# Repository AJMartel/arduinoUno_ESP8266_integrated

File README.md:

# Arduino UNO with built in ESP8266 Wifi Module
Arduino UNO with built in ESP8266 Wifi Module and 3.3v logic converter (pin outs added)

Created for 16Hertz LLC. 
Creative Commons Attribution/Non-Commercial/Share-Alike

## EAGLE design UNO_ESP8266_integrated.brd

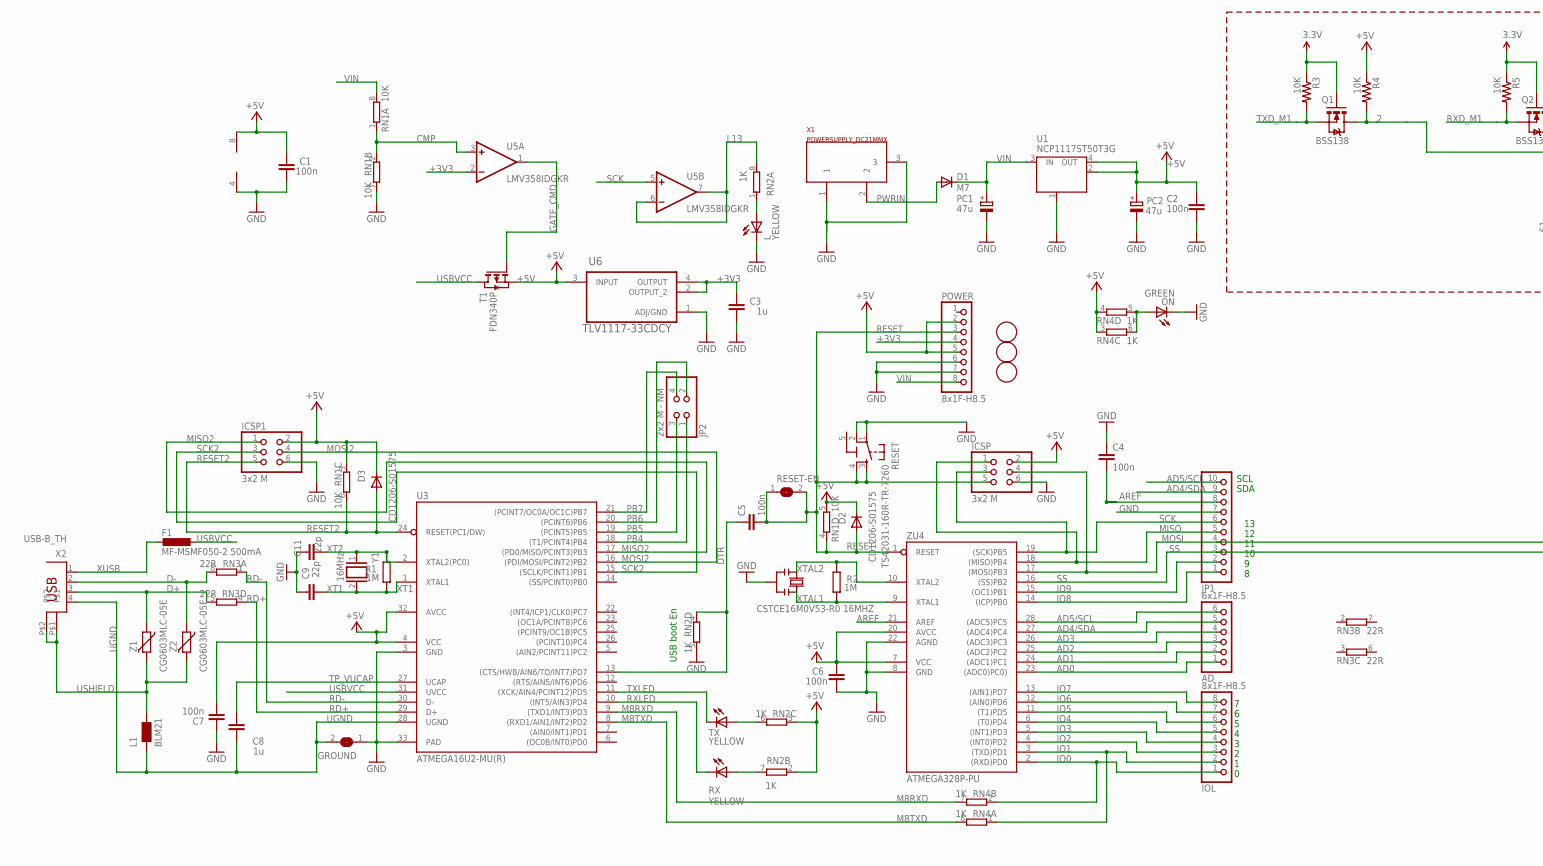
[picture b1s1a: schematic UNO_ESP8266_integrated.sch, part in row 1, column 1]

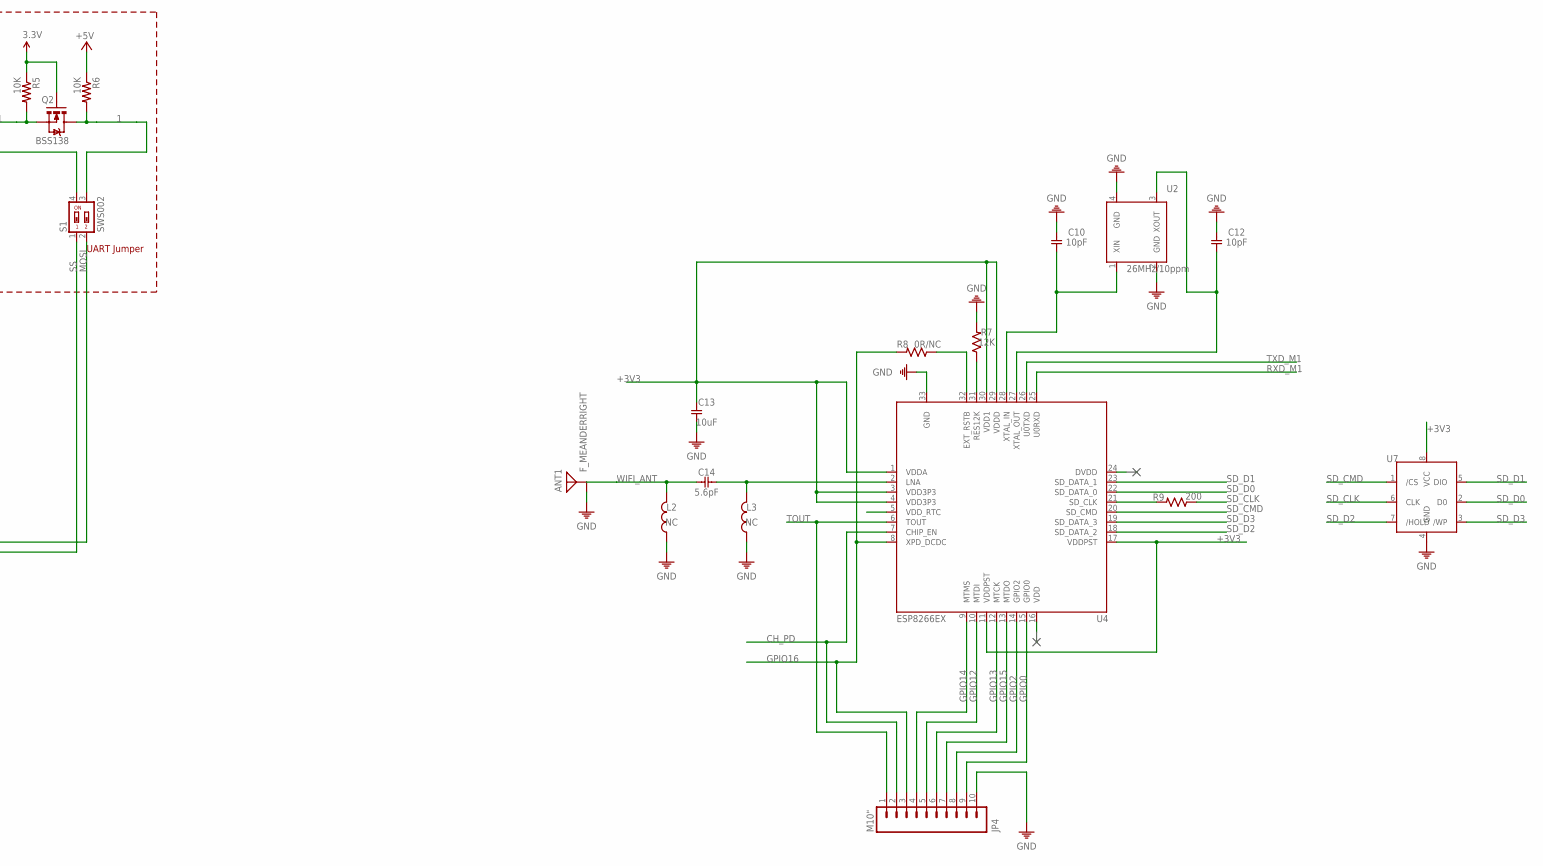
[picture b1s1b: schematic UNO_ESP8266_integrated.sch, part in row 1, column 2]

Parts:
AD: 6x1F-H8.5; 1X06
ANT1: F_MEANDERRIGHT; F_MEANDER_RIGHT
C1, C2, C4, C5, C6, C7: 100n; C0603-ROUND
C3, C8: 1u; C0603-ROUND
C9, C11: 22p; C0603-ROUND
C10, C12: 10pF; C0402
C13: 10uF; C0402
C14: 5.6pF; C0402
D1: M7; SMB
D2, D3: CD1206-S01575; MINIMELF
F1: MF-MSMF050-2 500mA; L1812
FD1, FD2, FD3: FIDUCIALMOUNT; FIDUCIA-MOUNT
GROUND: SJ
ICSP, ICSP1: 3x2 M; 2X03
IOL: 8x1F-H8.5; 1X08
JP1: PINHD-1X10_ARD; 1X10
JP2: 2x2 M - NM; 2X02
JP4: M10"; 1X10
L: YELLOW; CHIP-LED0805
L1: BLM21; 0805
L2, L3: NC; FB0603
ON: GREEN; CHIP-LED0805
PC1, PC2: 47u; PANASONIC_D
POWER: 8x1F-H8.5; 1X08
Q1, Q2: BSS138; SOT23-3
R1, R2: 1M; R0603-ROUND
R3, R4, R5, R6: 10K; 0603-RES
R7: 12K; R0402
R8: 0R/NC; R0402
R9: 200; R0402
RESET: TS42031-160R-TR-7260; TS42
RESET-EN: SJ
RN1: 10K; CAY16
RN2, RN4: 1K; CAY16
RN3: 22R; CAY16
RX: YELLOW; CHIP-LED0805
S1: SWS002; SMS-002
T1: FDN340P; SOT-23
TX: YELLOW; CHIP-LED0805
U1: NCP1117ST50T3G; SOT223
U2: 26MHz/10ppm; CRYSTAL_32X25
U3: ATMEGA16U2-MU(R); MLF32
U4: ESP8266EX; QFN32
U5: LMV358IDGKR; MSOP08
U6: TLV1117-33CDCY; SOT230P700X180-4N
U7: SPI_FLASH; SOIC-8
X1: POWERSUPPLY_DC21MMX; POWERSUPPLY_DC-21MM
X2: USB-B_TH; PN61729
Y1: 16MHz; QS
Y2: CSTCE16M0V53-R0 16MHZ; RESONATOR
Z1, Z2: CG0603MLC-05E; CT/CN0603
ZU4: ATMEGA328P-PU; DIL28-3

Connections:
1: Q2.3 (D), R6.2, S1.3
2: Q1.3 (D), R4.2, S1.4
5-GND: RESET.5 (5-GND)
+3V3: C3.2, C13.2, POWER.4, Q1.1 (G), Q2.1 (G), R3.1, R5.1, U4.1 (VDDA), U4.3 (VDD3P3), U4.4 (VDD3P3), U4.11 (VDDPST), U4.17 (VDDPST), U4.29 (VDDD), U4.30 (VDD1), U5.2 (-IN), U6.2 (OUTPUT_2), U6.4 (OUTPUT), U7.8 (VCC)
+5V: C1.2, C2.2, C6.2, C7.1, D2.C, D3.C, ICSP.2, ICSP1.2, PC2.+, POWER.2, POWER.5, R4.1, R6.1, RN1.3 (1), RN1.5 (2), RN2.2 (1), RN2.3 (1), RN4.3 (1), RN4.4 (1), T1.2 (S), U1.2 (OUT), U1.4 (OUT), U3.4 (VCC), U3.32 (AVCC), U5.8 (V+), U6.3 (INPUT), ZU4.7 (VCC), ZU4.20 (AVCC)
AD0: AD.1, ZU4.23 ((ADC0)PC0))
AD1: AD.2, ZU4.24 ((ADC1)PC1)
AD2: AD.3, ZU4.25 ((ADC2)PC2)
AD3: AD.4, ZU4.26 ((ADC3)PC3)
AD4/SDA: AD.5, JP1.9, ZU4.27 ((ADC4)PC4)
AD5/SCL: AD.6, JP1.10, ZU4.28 ((ADC5)PC5)
AREF: C4.2, JP1.8, ZU4.21 (AREF)
CH_PD: JP4.2, U4.7 (CHIP_EN)
CMP: RN1.1, RN1.2 (1), U5.3 (+IN)
D+: RN3.5 (2), X2.3, Z1.1
D-: RN3.8 (2), X2.2, Z2.1
DTR: C5.1, RN2.4 (1), U3.13 ((CTS/HWB/AIN6/TO/INT7)PD7)
GATE_CMD: T1.3 (G), U5.1 (OUT)
GND: ANT1.GND, C1.1, C2.1, C3.1, C4.1, C6.1, C7.2, C9.2, C10.2, C11.2, C12.2, C13.1, GROUND.1, ICSP.6, ICSP1.6, JP1.7, JP4.10, L.C, L2.1, L3.1, ON.C, PC1.-, PC2.-, POWER.6, POWER.7, R7.2, RESET.1, RESET.2, RN1.7 (2), RN2.5 (2), U1.1 (GND/ADJ), U2.2 (GND), U2.4 (GND), U3.3 (GND), U3.33 (PAD), U4.33 (GND), U5.4 (V-), U6.1 (ADJ/GND), U7.4 (GND), X1.1, X1.3, Y2.2, ZU4.8 (GND), ZU4.22 (AGND)
GPIO0: JP4.9, U4.15 (GPIO0)
GPIO2: JP4.8, U4.14 (GPIO2)
GPIO12: JP4.5, U4.10 (MTDI)
GPIO13: JP4.6, U4.12 (MTCK)
GPIO14: JP4.4, U4.9 (MTMS)
GPIO15: JP4.7, U4.13 (MTDO)
GPIO16: JP4.3, R8.2, U4.8 (XPD_DCDC)
IO0: IOL.1, RN4.2 (1), ZU4.2 ((RXD)PD0)
IO1: IOL.2, RN4.1, ZU4.3 ((TXD)PD1)
IO2: IOL.3, ZU4.4 ((INT0)PD2)
IO3: IOL.4, ZU4.5 ((INT1)PD3)
IO4: IOL.5, ZU4.6 ((T0)PD4)
IO5: IOL.6, ZU4.11 ((T1)PD5)
IO6: IOL.7, ZU4.12 ((AIN0)PD6)
IO7: IOL.8, ZU4.13 ((AIN1)PD7)
IO8: JP1.1, ZU4.14 ((ICP)PB0)
IO9: JP1.2, ZU4.15 ((OC1)PB1)
L13: RN2.8 (2), U5.6 (-IN), U5.7 (OUT)
M8RXD: RN4.7 (2), U3.9 ((TXD1/INT3)PD3)
M8TXD: RN4.8 (2), U3.8 ((RXD1/AIN1/INT2)PD2)
MISO: ICSP.1, JP1.5, ZU4.18 ((MISO)PB4)
MISO2: ICSP1.1, U3.17 ((PD0/MISO/PCINT3)PB3)
MOSI: ICSP.4, JP1.4, S1.2, ZU4.17 ((MOSI)PB3)
MOSI2: ICSP1.4, U3.16 ((PDI/MOSI/PCINT2)PB2)
unnamed: L.A, RN2.1
unnamed: R8.1, U4.32 (EXT_RSTB)
unnamed: ON.A, RN4.5 (2), RN4.6 (2)
unnamed: R7.1, U4.31 (RES12K)
unnamed: C14.1, L3.2, U4.2 (LNA)
unnamed: C10.1, U2.1 (XIN), U4.28 (XTAL_IN)
unnamed: R9.2, U4.21 (SD_CLK)
unnamed: C12.1, U2.3 (XOUT), U4.27 (XTAL_OUT)
unnamed: RN2.7 (2), RX.A
unnamed: RN2.6 (2), TX.A
PB4: JP2.1, U3.18 ((T1/PCINT4)PB4)
PB5: JP2.3, U3.19 ((PCINT5)PB5)
PB6: JP2.2, U3.20 ((PCINT6)PB6)
PB7: JP2.4, U3.21 ((PCINT7/OC0A/OC1C)PB7)
PWRIN: D1.A, X1.2
RD+: RN3.4 (1), U3.29 (D+)
RD-: RN3.1, U3.30 (D-)
RESET: C5.2, D2.A, ICSP.5, POWER.3, RESET.3, RESET.4, RESET-EN.1, RESET-EN.2, RN1.4 (1), ZU4.1 (RESET)
RESET2: D3.A, ICSP1.5, RN1.6 (2), U3.24 (RESET(PC1/DW))
RXD_M1: Q2.2 (S), R5.2, U4.25 (U0RXD)
RXLED: RX.C, U3.10 ((INT5/AIN3)PD4)
SCK: ICSP.3, JP1.6, U5.5 (+IN), ZU4.19 ((SCK)PB5)
SCK2: ICSP1.3, U3.15 ((SCLK/PCINT1)PB1)
SD_CLK: R9.1, U7.6 (CLK)
SD_CMD: U4.20 (SD_CMD), U7.1 (/CS)
SD_D0: U4.22 (SD_DATA_0), U7.2 (D0)
SD_D1: U4.23 (SD_DATA_1), U7.5 (DIO)
SD_D2: U4.18 (SD_DATA_2), U7.7 (/HOLD)
SD_D3: U4.19 (SD_DATA_3), U7.3 (/WP)
SS: JP1.3, S1.1, ZU4.16 ((SS)PB2)
TOUT: JP4.1, U4.6 (TOUT)
TP_VUCAP: C8.1, U3.27 (UCAP)
TXD_M1: Q1.2 (S), R3.2, U4.26 (U0TXD)
TXLED: TX.C, U3.11 ((XCK/AIN4/PCINT12)PD5)
UGND: C8.2, GROUND.2, L1.1, U3.28 (UGND), X2.4
USBVCC: F1.1, T1.1 (D), U3.31 (UVCC)
USHIELD: L1.2, X2.P$1, X2.P$2, Z1.2, Z2.2
VIN: D1.C, PC1.+, POWER.8, RN1.8 (2), U1.3 (IN)
WIFI_ANT: ANT1.RF, C14.2, L2.2
XT1: C9.1, R1.1, U3.1 (XTAL1), Y1.2
XT2: C11.1, R1.2, U3.2 (XTAL2(PC0)), Y1.1
XTAL1: R2.1, Y2.3, ZU4.9 (XTAL1)
XTAL2: R2.2, Y2.1, ZU4.10 (XTAL2)
XUSB: F1.2, X2.1

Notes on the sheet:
USB boot En
SDA
SCL
UART Jumper

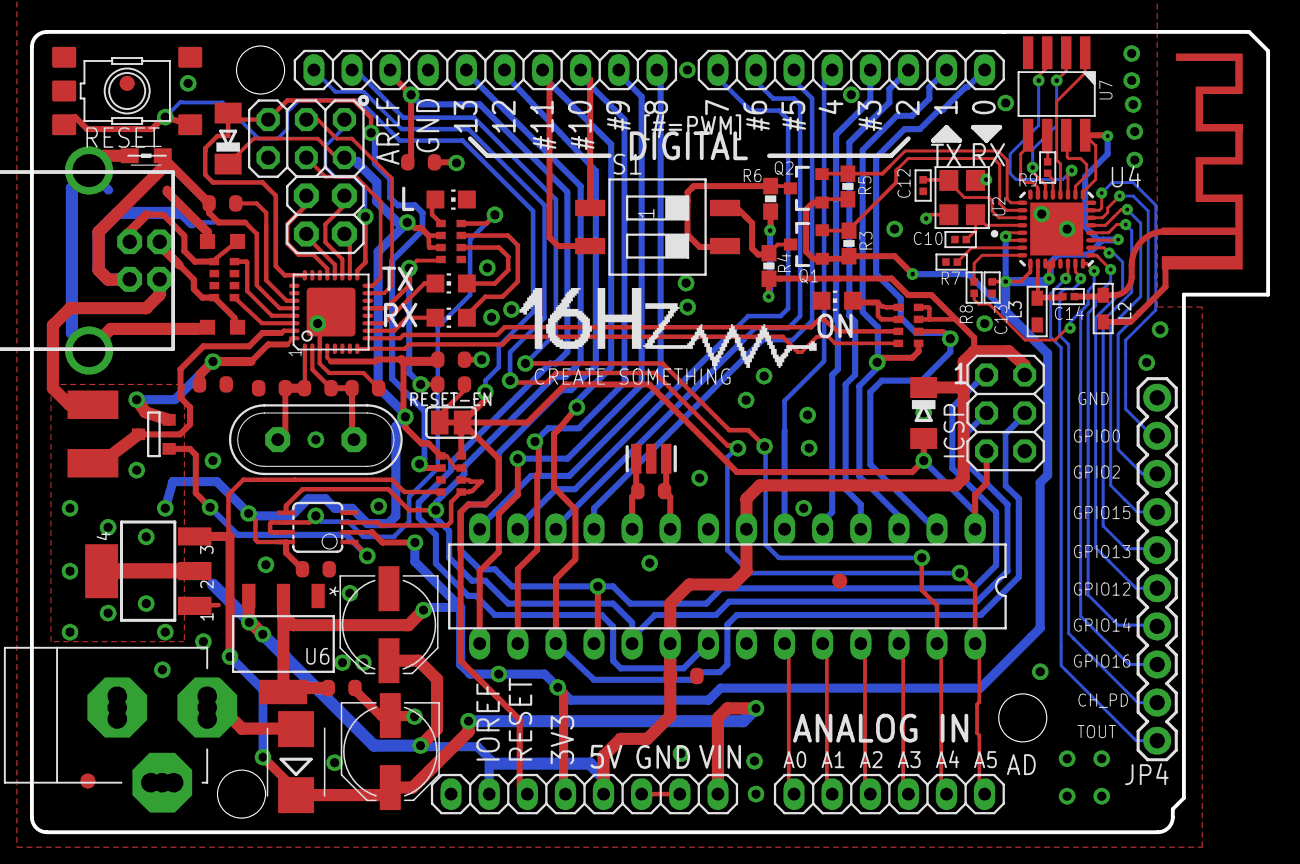
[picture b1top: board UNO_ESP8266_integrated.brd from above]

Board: 2 copper layers, 82.4 x 53.3 mm, 73 parts (1 on the bottom side), 86 nets.

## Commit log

2016-02-24 Logic converted added

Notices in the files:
parts and their libraries:
SparkFun-Connectors: Licensing: CC v3.0 Share-Alike You are welcome to use this library for commercial purposes.
